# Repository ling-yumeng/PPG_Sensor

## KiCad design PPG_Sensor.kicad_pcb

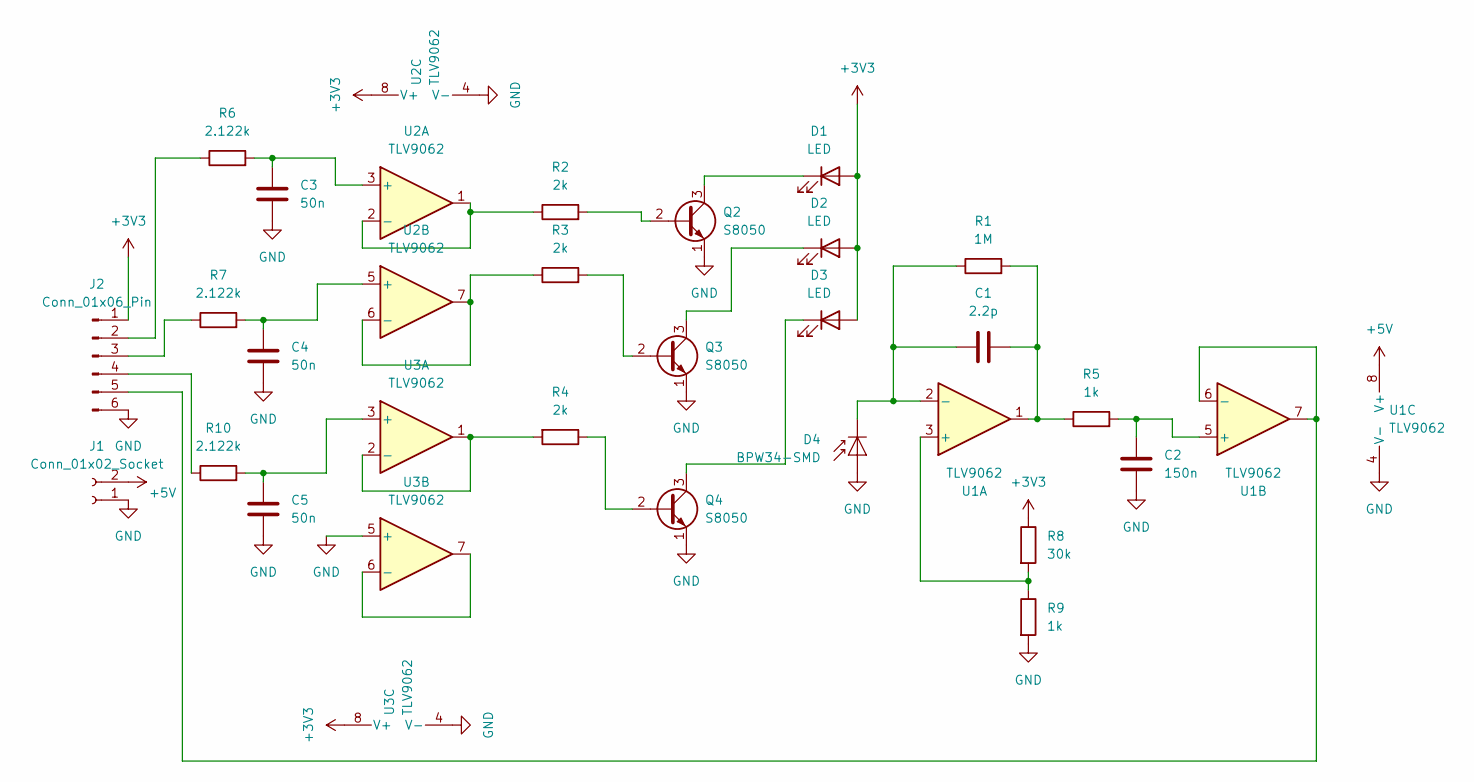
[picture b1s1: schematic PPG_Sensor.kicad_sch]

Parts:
C1: 2.2p; C_0603_1608Metric
C2: 150n; C_0603_1608Metric
C3, C4, C5: 50n; C_0603_1608Metric
D1, D2, D3: LED; LED_0402_1005Metric
D4: BPW34-SMD; Osram_BPW34S-SMD
J1: Conn_01x02_Socket; PinSocket_1x02_P2.54mm_Horizontal
J2: Conn_01x06_Pin; PinSocket_1x06_P2.54mm_Horizontal
Q2, Q3, Q4: S8050; TO-92_Inline
R1: 1M; R_0603_1608Metric
R2, R3, R4: 2k; R_0603_1608Metric
R5, R9: 1k; R_0603_1608Metric
R6, R7, R10: 2.122k; R_0603_1608Metric
R8: 30k; R_0603_1608Metric
U1, U2, U3: TLV9062; SOIC-8_3.9x4.9mm_P1.27mm

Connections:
+3V3: D1.2 (A), D2.2 (A), D3.2 (A), J2.1, R8.1, U2.8 (V+), U3.8 (V+)
+5V: J1.2, U1.8 (V+)
GND: C2.2, C3.2, C4.2, C5.2, D4.2 (A), J1.1, J2.6, Q2.1 (E), Q3.1 (E), Q4.1 (E), R9.2, U1.4 (V-), U2.4 (V-), U3.4 (V-), U3.5 (+)
unnamed: C1.2, R1.2, R5.1, U1.1
unnamed: D1.1 (K), Q2.3 (C)
unnamed: D2.1 (K), Q3.3 (C)
unnamed: D3.1 (K), Q4.3 (C)
unnamed: C1.1, D4.1 (K), R1.1, U1.2 (-)
unnamed: J2.2, R6.1
unnamed: J2.3, R7.1
unnamed: J2.4, R10.1
unnamed: J2.5, U1.6 (-), U1.7
unnamed: Q2.2 (B), R2.2
unnamed: Q3.2 (B), R3.2
unnamed: Q4.2 (B), R4.1
unnamed: R8.2, R9.1, U1.3 (+)
unnamed: C2.1, R5.2, U1.5 (+)
unnamed: C3.1, R6.2, U2.3 (+)
unnamed: R2.1, U2.1, U2.2 (-)
unnamed: C4.1, R7.2, U2.5 (+)
unnamed: R3.1, U2.6 (-), U2.7
unnamed: C5.1, R10.2, U3.3 (+)
unnamed: R4.2, U3.1, U3.2 (-)
unnamed: U3.6 (-), U3.7

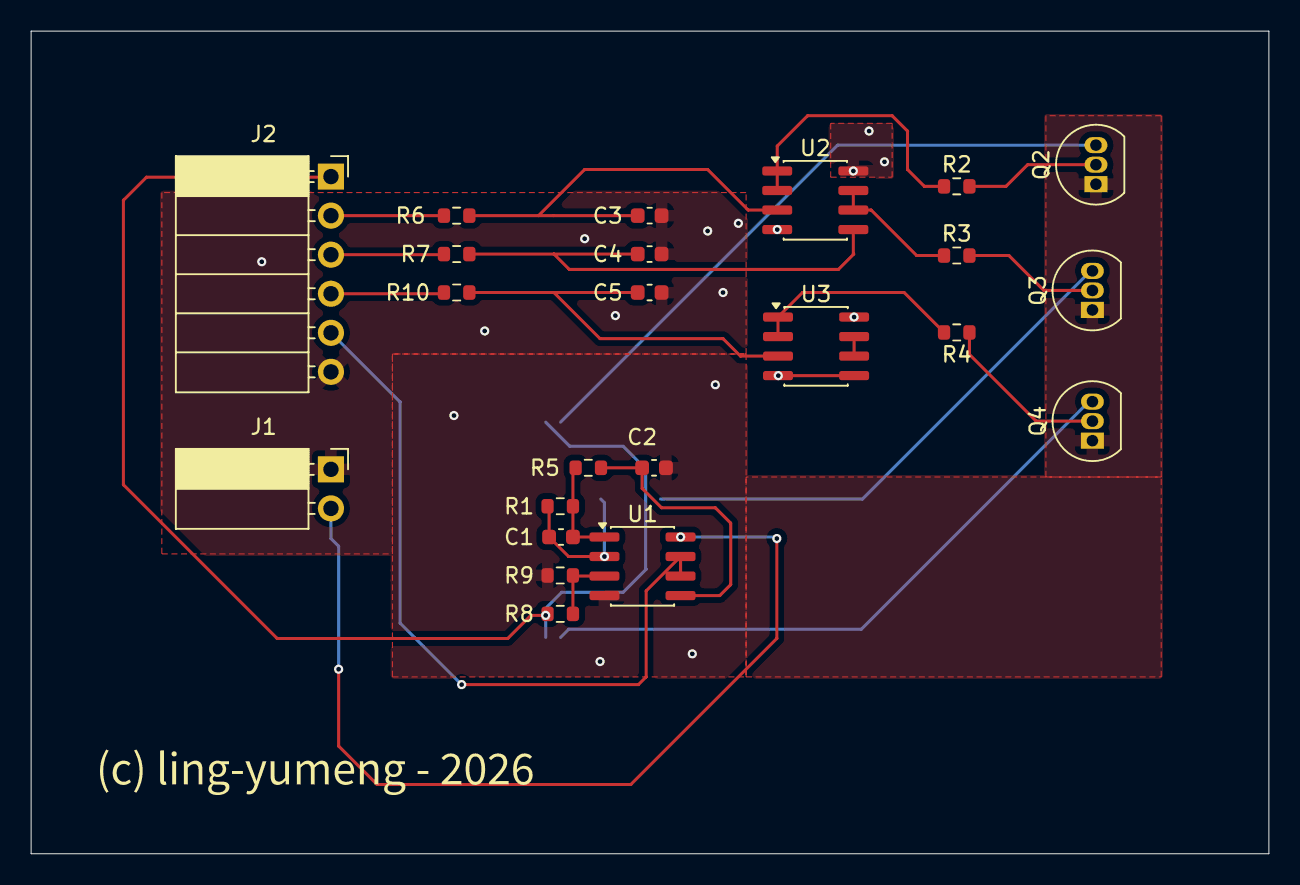
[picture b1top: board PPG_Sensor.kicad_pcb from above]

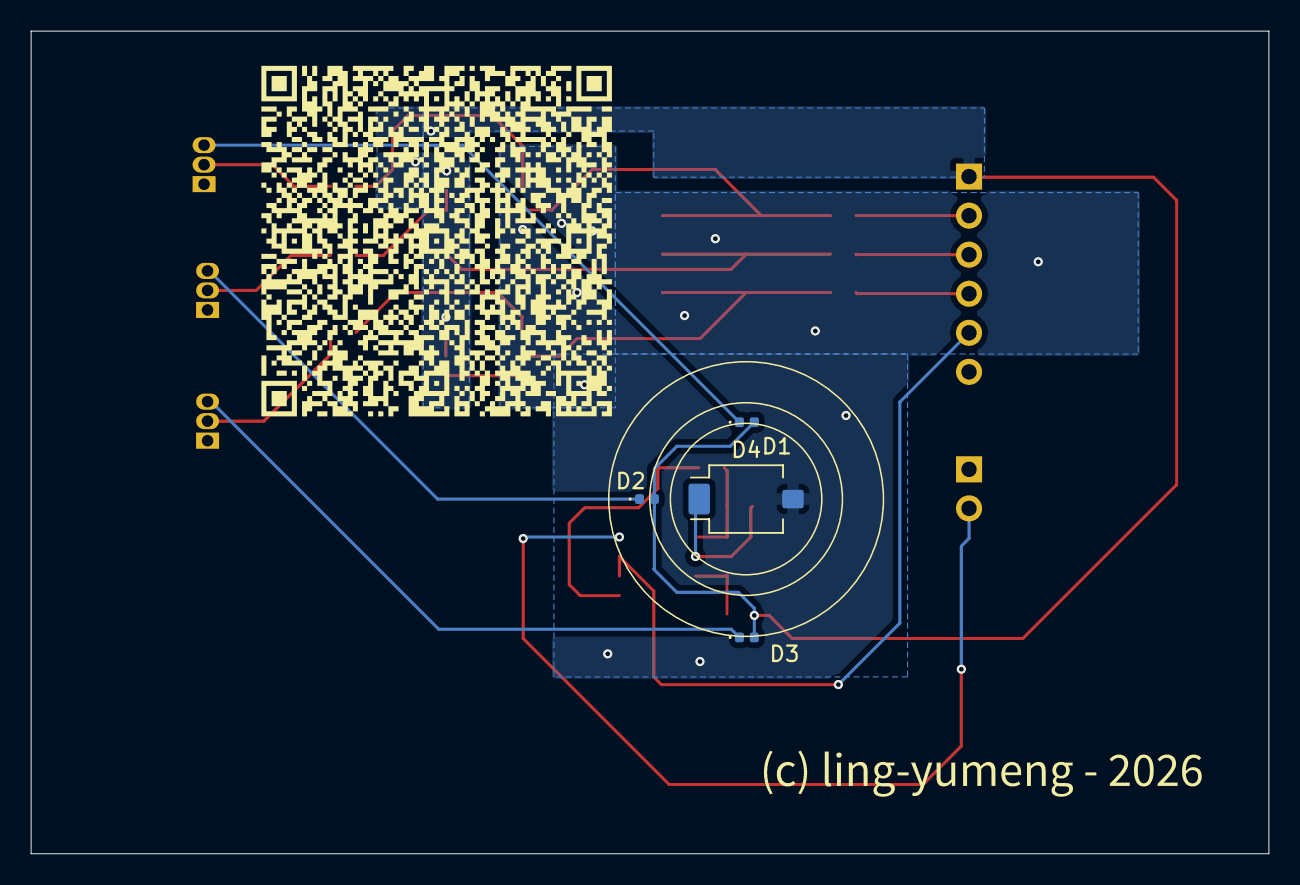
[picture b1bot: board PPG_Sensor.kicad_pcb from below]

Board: 2 copper layers, 80.5 x 53.5 mm, 27 parts (4 on the bottom side), 24 nets.
